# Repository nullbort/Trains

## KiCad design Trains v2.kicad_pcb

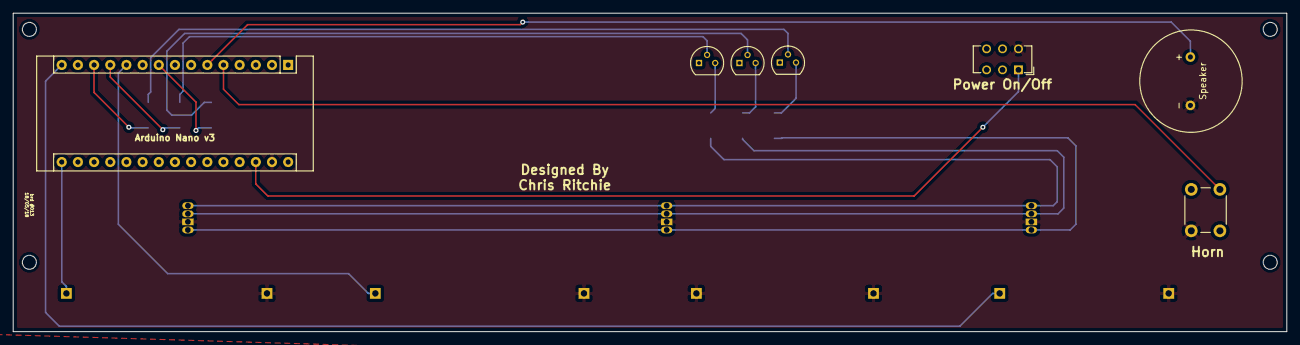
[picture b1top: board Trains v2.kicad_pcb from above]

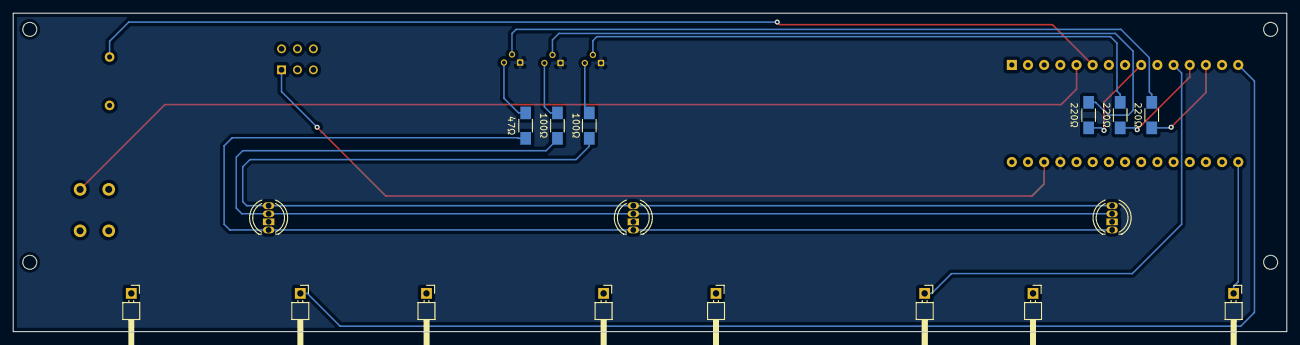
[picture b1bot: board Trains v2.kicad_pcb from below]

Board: 2 copper layers, 200.0 x 50.0 mm, 24 parts (17 on the bottom side), 20 nets.

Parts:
A1: Arduino_Nano_v3.x; Arduino_Nano
D1, D2, D3: LED_CRGB; LED_D5.0mm-4
LS1: Speaker; CVS-1508 Speaker
MK1, MK2, MK3, MK4, MK5, MK6, MK7, MK8: Pin; Pin_Header_Angled_1x01_Pitch2.54mm
Q1, Q2, Q3: 2N3904; TO-92_Molded_Narrow
R1, R2, R3, R4, R5, R6: R; R_1206_HandSoldering
SW1: SW_SPST4; SW_CuK_JS202011CQN_DPDT_Straight
SW2: SW_SPST4; SW_PUSH_6mm

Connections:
/5V: A1.27, Q1.1, Q2.1, Q3.1
/B_OUT: D1.3, D2.3, D3.3, R3.2
/Boxcar_LED: A1.15, MK7.1
/Caboose_LED: A1.11, MK3.1
/Engine_LED: A1.16, MK1.1
/GND: A1.29, D1.2, D2.2, D3.2, LS1.2, MK2.1, MK4.1, MK5.1, MK6.1, MK8.1, SW1.4, SW2.4
/G_OUT: D1.4, D2.4, D3.4, R2.2
/LED_B: A1.9, R6.1
/LED_G: A1.12, R5.1
/LED_R: A1.13, R4.1
/Power_Button: A1.28, SW1.1
/R_OUT: D1.1, D2.1, D3.1, R1.2
/Speaker_Button: A1.5, SW2.1
/Speaker_Pin: A1.6, LS1.1
unnamed: Q1.2, R4.2
unnamed: Q1.3, R1.1
unnamed: Q2.2, R5.2
unnamed: Q2.3, R2.1
unnamed: Q3.2, R6.2
unnamed: Q3.3, R3.1

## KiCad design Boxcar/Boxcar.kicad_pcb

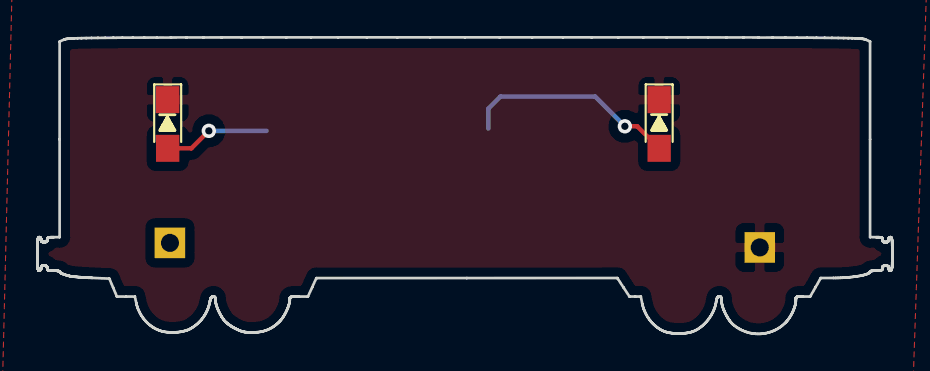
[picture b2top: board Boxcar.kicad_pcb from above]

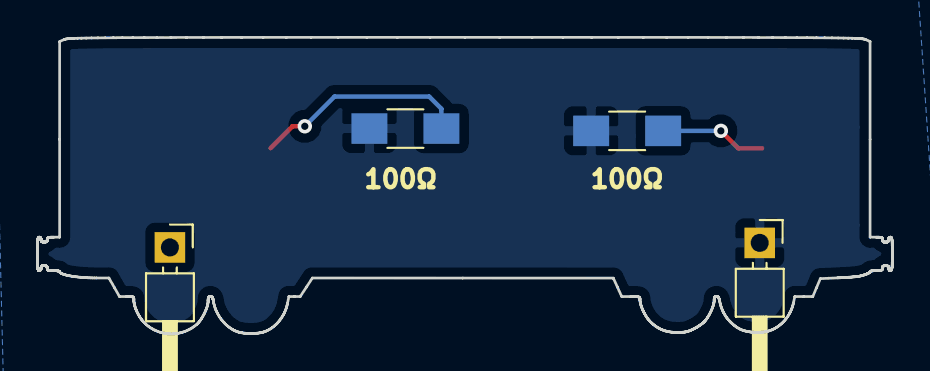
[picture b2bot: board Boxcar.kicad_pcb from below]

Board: 2 copper layers, 47.5 x 16.5 mm, 6 parts (4 on the bottom side), 4 nets.

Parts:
D1, D2: LED; LED_0805_HandSoldering
MK1: VCC; Pin_Header_Angled_1x01_Pitch2.54mm
MK2: GND; Pin_Header_Angled_1x01_Pitch2.54mm
R1, R2: R; R_1206_HandSoldering

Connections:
/GND: D1.1, D2.1, MK2.1
/VCC: MK1.1, R1.2, R2.2
unnamed: D1.2, R1.1
unnamed: D2.2, R2.1

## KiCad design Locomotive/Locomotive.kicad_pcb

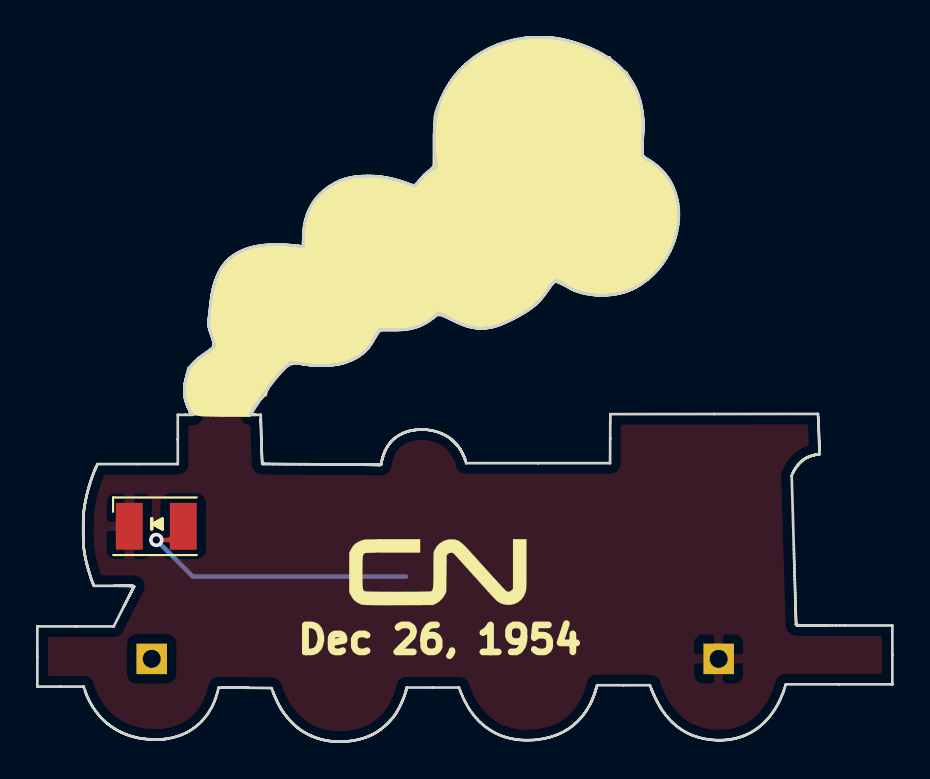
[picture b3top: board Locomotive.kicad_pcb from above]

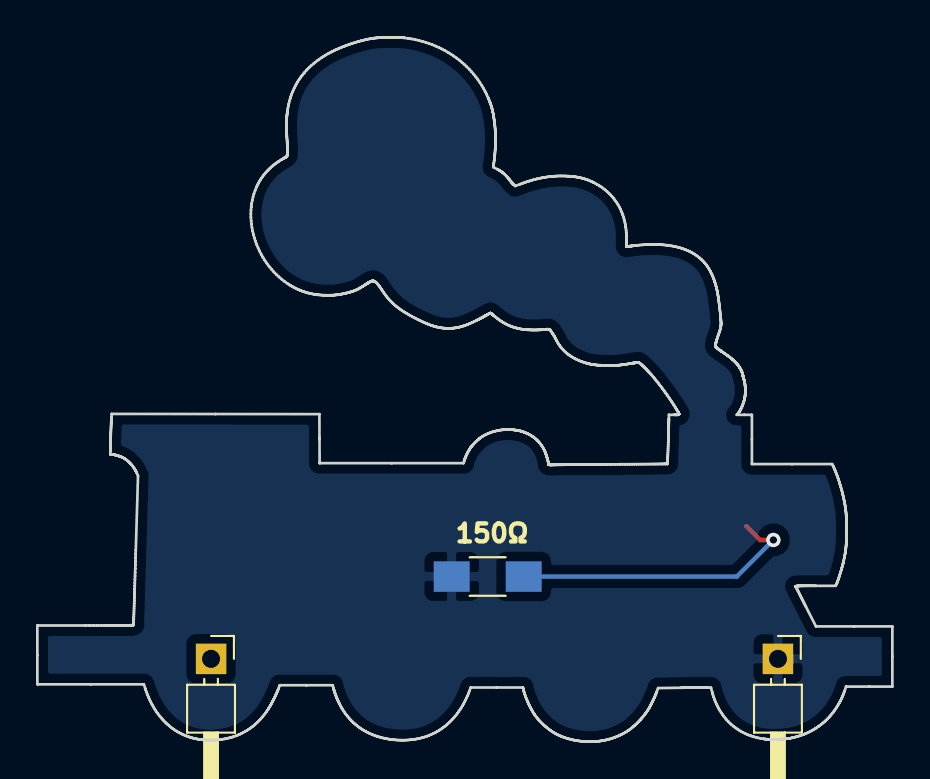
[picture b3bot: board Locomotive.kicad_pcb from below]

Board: 2 copper layers, 47.5 x 39.1 mm, 6 parts (3 on the bottom side), 3 nets.

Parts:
CNLogo: LOGO; CN-Large
D1: LED; LED_PLCC-2
MK1: VCC; Pin_Header_Angled_1x01_Pitch2.54mm
MK2: GND; Pin_Header_Angled_1x01_Pitch2.54mm
R1: R; R_1206_HandSoldering
Steam: LOGO; Steam

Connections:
/GND: D1.1, MK2.1
/VCC: MK1.1, R1.2
unnamed: D1.2, R1.1

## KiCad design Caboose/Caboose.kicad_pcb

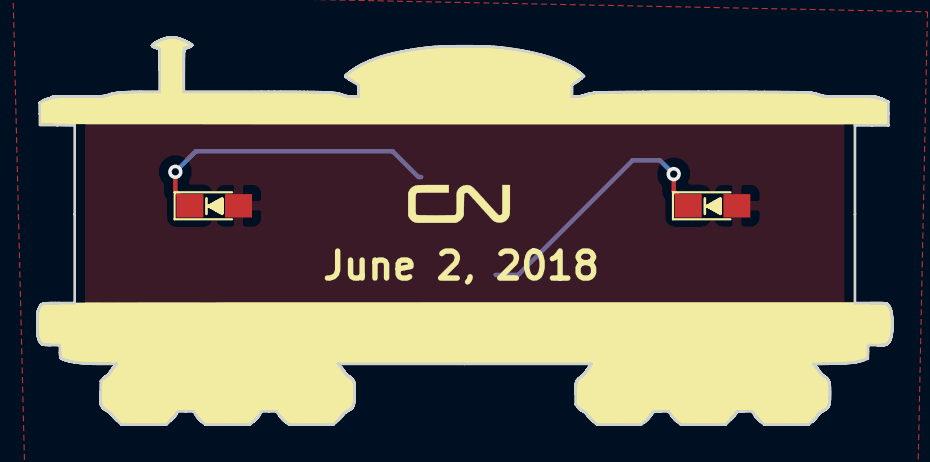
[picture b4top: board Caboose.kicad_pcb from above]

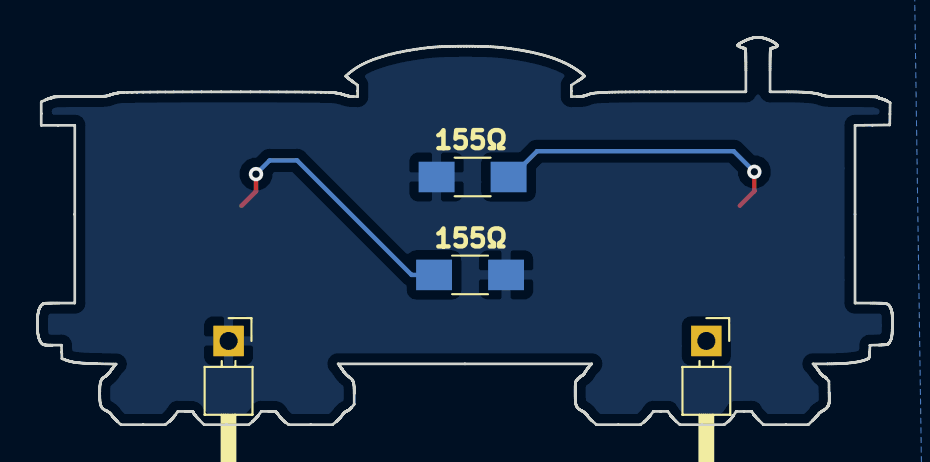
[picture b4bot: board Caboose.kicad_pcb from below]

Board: 2 copper layers, 47.5 x 21.5 mm, 6 parts (4 on the bottom side), 4 nets.

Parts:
D1, D2: LED; LED_0805_HandSoldering
MK1: VCC; Pin_Header_Angled_1x01_Pitch2.54mm
MK2: GND; Pin_Header_Angled_1x01_Pitch2.54mm
R1, R2: R; R_1206_HandSoldering

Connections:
/GND: MK2.1, R1.1, R2.1
/VCC: D1.2, D2.2, MK1.1
unnamed: D1.1, R1.2
unnamed: D2.1, R2.2

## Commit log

2018-05-04 Add Files
2018-05-04 Add & Align Pins
    Add pins to all trains and set proper locations
    Move RGB LEDs and resistors
    Connect RGB LEDs to resistors and speaker to Arduino
2018-05-10 Connect Trains
2018-05-12 Change Schematic For RGB LEDs
    Add transistors to control 3 RGB LEDs
    Add Silkscreen detail to caboose
2018-05-18 Finalize Tracks
    Finish tracks for 3 RGB LEDs
    Move date to locomotive, remove from caboose
2018-05-18 Add Acrylic Base
    Add acrylic base
    Add board #
2019-04-11 Update Text
    Change dates on trains
